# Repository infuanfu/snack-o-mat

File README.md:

snack-o-mat
===========

repo for repairing of the snack-vending machine @shackspace

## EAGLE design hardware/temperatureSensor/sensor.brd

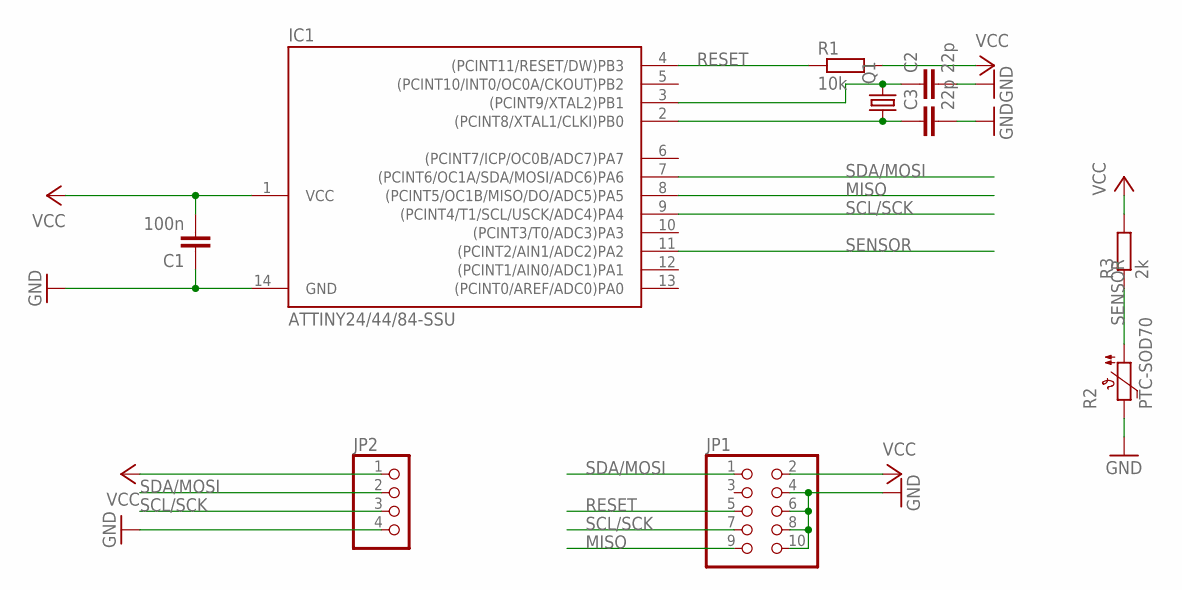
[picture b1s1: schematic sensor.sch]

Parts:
C1: 100n; C0805
C2, C3: 22p; C0805
IC1: ATTINY24/44/84-SSU; SOIC14
JP1: PINHD-2X5; 2X05
JP2: PINHD-1X4; 1X04
Q1: CRYSTALHC49UP; HC49UP
R1: 10k; M0805
R2: PTC-SOD70; SOD70
R3: 2k; M0805

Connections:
GND: C1.1, C2.2, C3.2, IC1.14 (GND), JP1.4, JP1.6, JP1.8, JP1.10, JP2.4, R2.2
MISO: IC1.8 ((PCINT5/OC1B/MISO/DO/ADC5)PA5), JP1.9
unnamed: C2.1, IC1.3 ((PCINT9/XTAL2)PB1), Q1.2
unnamed: C3.1, IC1.2 ((PCINT8/XTAL1/CLKI)PB0), Q1.1
RESET: IC1.4 ((PCINT11/RESET/DW)PB3), JP1.5, R1.1
SCL/SCK: IC1.9 ((PCINT4/T1/SCL/USCK/ADC4)PA4), JP1.7, JP2.3
SDA/MOSI: IC1.7 ((PCINT6/OC1A/SDA/MOSI/ADC6)PA6), JP1.1, JP2.2
SENSOR: IC1.11 ((PCINT2/AIN1/ADC2)PA2), R2.1, R3.1
VCC: C1.2, IC1.1 (VCC), JP1.2, JP2.1, R1.2, R3.2

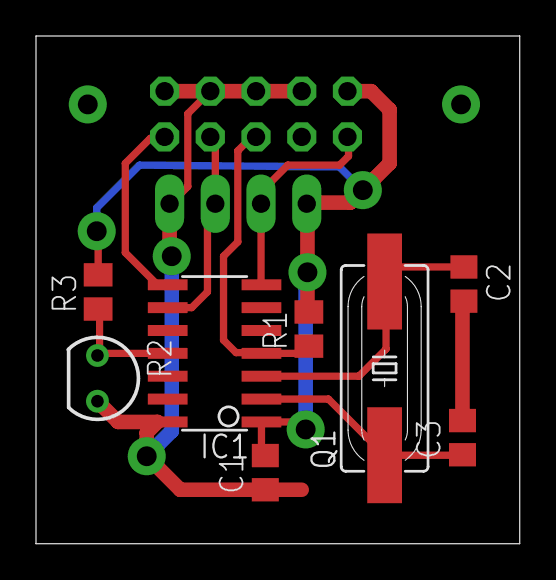
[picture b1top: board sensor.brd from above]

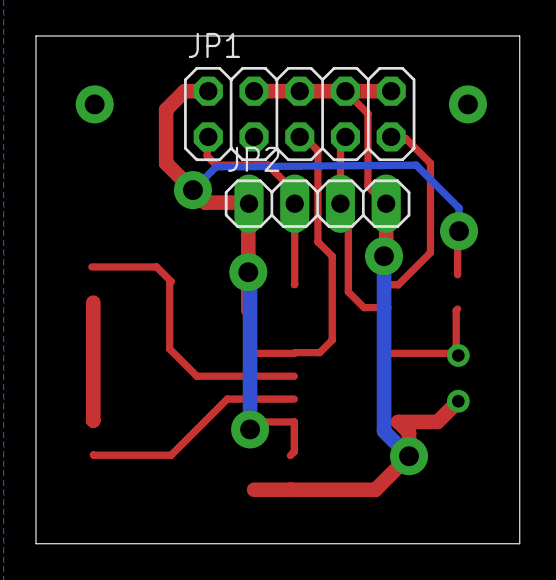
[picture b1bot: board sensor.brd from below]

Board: 2 copper layers, 26.9 x 28.2 mm, 10 parts (2 on the bottom side), 9 nets.

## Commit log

2013-03-18 version 1: the display works with the old functionality again
2013-03-22 cleanup of old repo structure, extended namespace for more modules.
2013-03-22 hardware design
2013-03-27 changed firmware of display to be interrupt driven instead of polling in a busy loop
